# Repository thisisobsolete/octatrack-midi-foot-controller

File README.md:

# octatrack-midi-foot-controller
MIDI foot controller for Elektron Octatrack DPS-1

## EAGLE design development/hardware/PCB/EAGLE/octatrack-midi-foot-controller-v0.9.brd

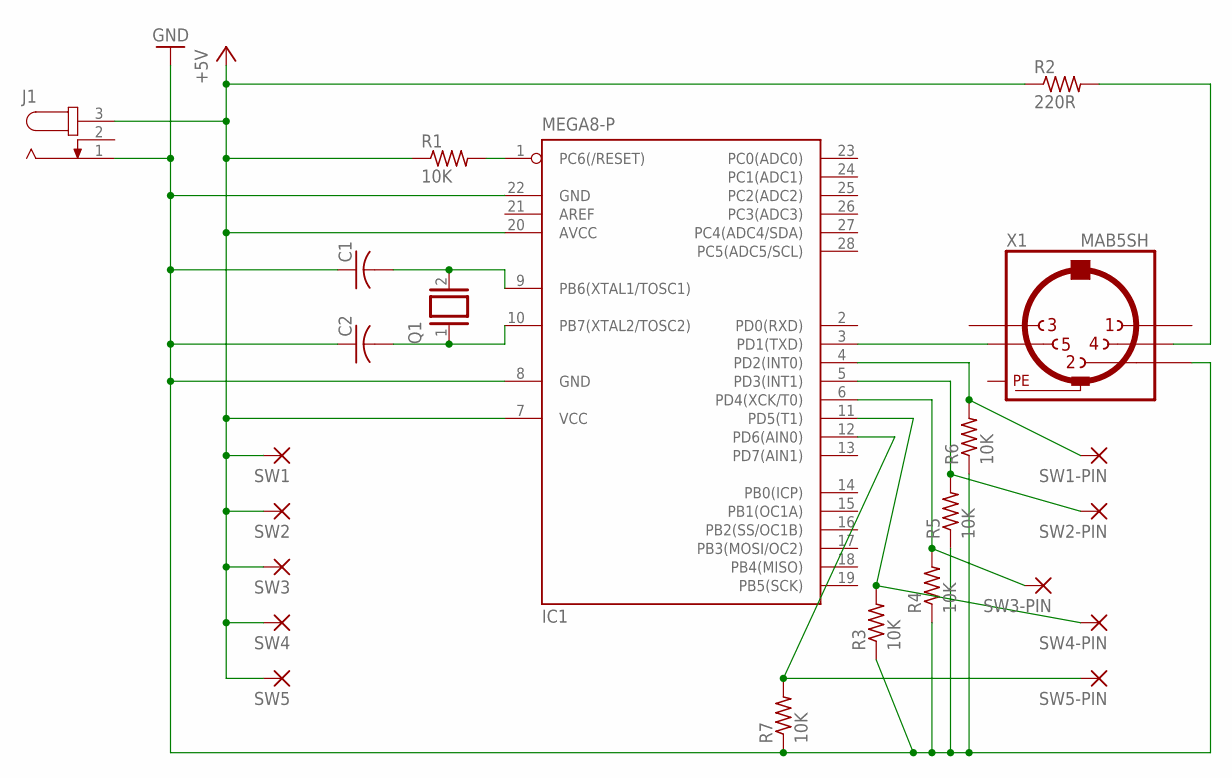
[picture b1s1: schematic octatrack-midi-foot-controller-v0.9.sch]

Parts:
C1, C2: C-US025-025X050; C025-025X050
IC1: MEGA8-P; DIL28-3
J1: JACK-PLUG0; SPC4077
Q1: XTAL; Q
R1, R3, R4, R5, R6, R7: 10K; 0204/7
R2: 220R; 0204/7
SW1, SW1-PIN, SW2, SW2-PIN, SW3, SW3-PIN, SW4, SW4-PIN, SW5, SW5-PIN: WIREPAD3,17/1,1; 3,17/1,1
X1: MAB5SH

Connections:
+5V: IC1.7 (VCC), IC1.20 (AVCC), J1.3, R1.1, R2.1, SW1.1, SW2.1, SW3.1, SW4.1, SW5.1
GND: C1.1, C2.1, IC1.8 (GND), IC1.22 (GND), J1.1, R3.1, R4.1, R5.1, R6.1, R7.1, X1.2
unnamed: IC1.3 (PD1(TXD)), X1.5
unnamed: IC1.1 (PC6(/RESET)), R1.2
unnamed: R2.2, X1.4
unnamed: IC1.4 (PD2(INT0)), R6.2, SW1-PIN.1
unnamed: C1.2, IC1.9 (PB6(XTAL1/TOSC1)), Q1.2
unnamed: C2.2, IC1.10 (PB7(XTAL2/TOSC2)), Q1.1
unnamed: IC1.5 (PD3(INT1)), R5.2, SW2-PIN.1
unnamed: IC1.6 (PD4(XCK/T0)), R4.2, SW3-PIN.1
unnamed: IC1.11 (PD5(T1)), R3.2, SW4-PIN.1
unnamed: IC1.12 (PD6(AIN0)), R7.2, SW5-PIN.1
PE: X1.PE, X1.PE@ (PE)

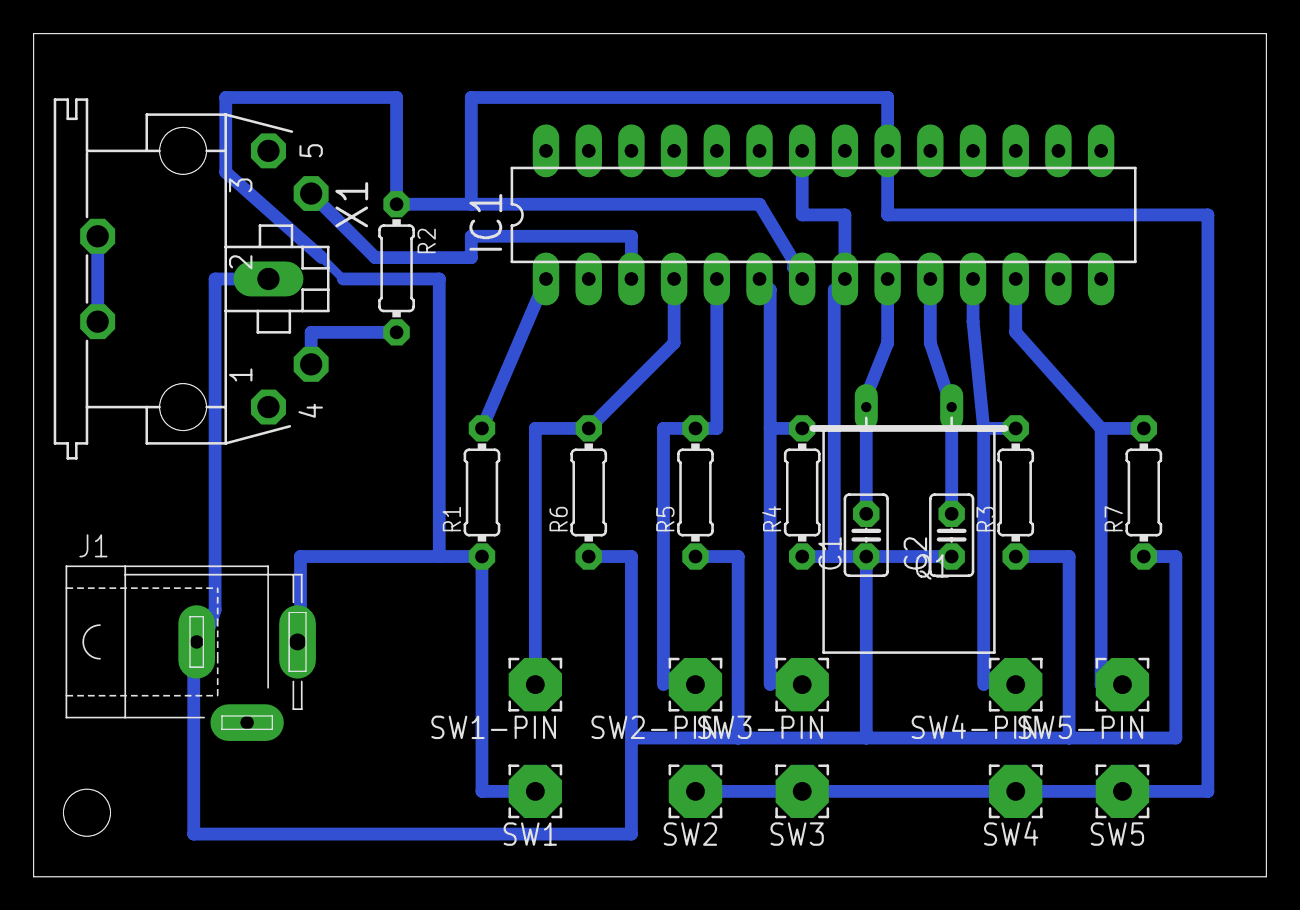
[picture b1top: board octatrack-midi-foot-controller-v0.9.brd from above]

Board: 2 copper layers, 73.3 x 50.2 mm, 23 parts (0 on the bottom side), 13 nets.

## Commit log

2015-05-02 Arduino IDE reconfigured it's save folders
